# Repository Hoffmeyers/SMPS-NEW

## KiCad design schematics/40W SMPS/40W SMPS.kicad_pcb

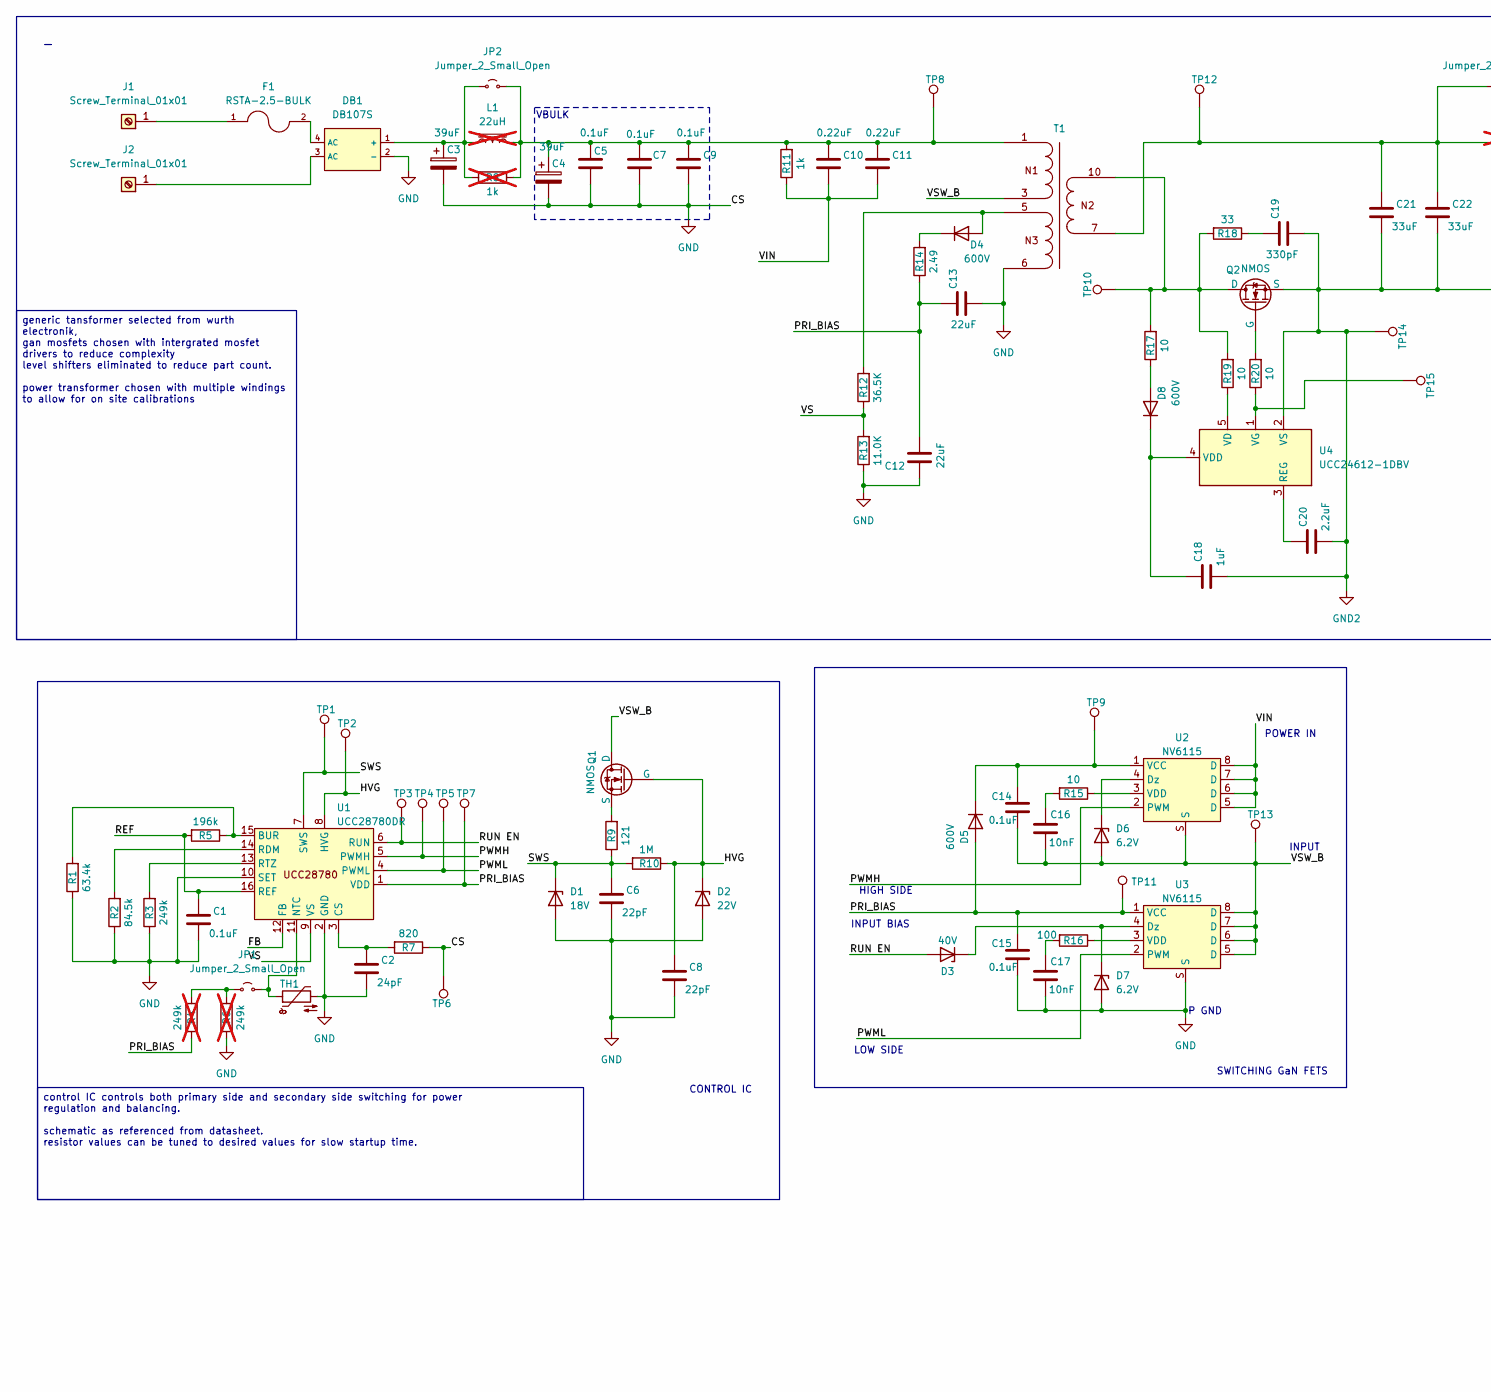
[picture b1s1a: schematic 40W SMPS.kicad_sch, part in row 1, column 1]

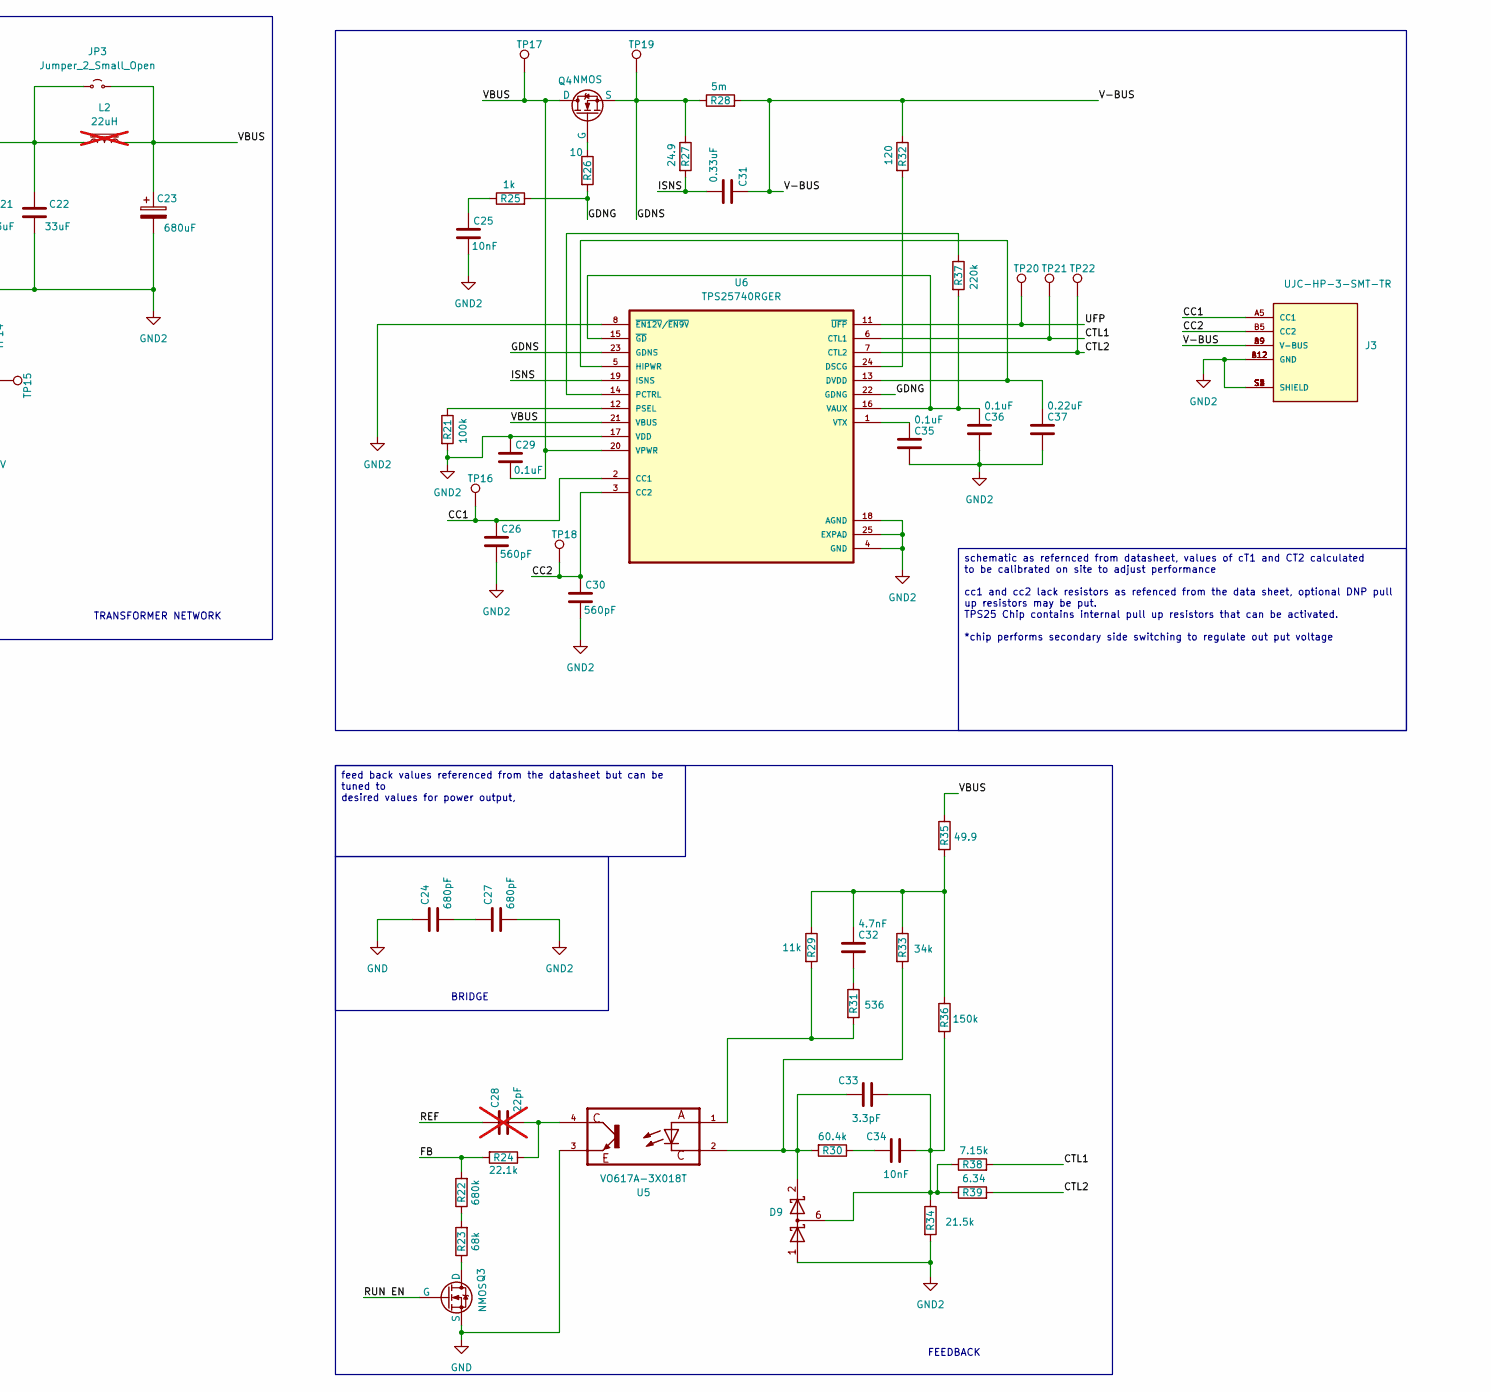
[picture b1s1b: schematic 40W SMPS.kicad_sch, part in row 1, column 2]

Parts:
C1, C5, C7, C9, C14, C15, C29, C35, C36: 0.1uF; C_0603; LCSC C14663
C2: 24pF; C_0603; LCSC C1654
C3, C4: 39uF; CP_Radial_D8.0mm_P3.80mm; LCSC C6718369
C6, C8: 22pF; C_0603; LCSC C1653
C10, C11, C37: 0.22uF; C_0603; LCSC C64705
C12, C13: 22uF; C_0603; LCSC C86295
C16, C17, C25, C34: 10nF; C_0603; LCSC C100042
C18: 1uF; C_0603; LCSC C15849
C19: 330pF; C_0603; LCSC C62784
C20: 2.2uF; C_0603; LCSC C23630
C21, C22: 33uF; C_CASE-A-3216-18(mm); LCSC C7186
C23: 680uF; CP_Radial_D8.0mm_P3.80mm; LCSC C88760
C24, C27: 680pF; C_0603; LCSC C30816
C26, C30: 560pF; C_0603; LCSC C519565
C28: 22pF; C_0603; LCSC C1653; not fitted
C31: 0.33uF; C_0603; LCSC C7419419
C32: 4.7nF; C_0603; LCSC C1621
C33: 3.3pF; C_0603; LCSC C882553
D1: 18V; SBR130S3-7; LCSC C117949
D2: 22V; SBR130S3-7; LCSC C117949
D3: 40V; DIO_MBRAD1045H; LCSC C19852660
D4, D5, D8: 600V; D_0603_1608Metric; LCSC C142698
D6, D7: 6.2V; SBR130S3-7; LCSC C117949
D9: D_Schottky_Dual_Series_CAK; SOT-363_SC-70-6; LCSC C96225
DB1: DB107S; DBS_L8.2-W6.4-P5.10-LS10.0-BL; Reverse Voltage (Vr) 1kV; Forward Voltage (Vf@If) 1.1V@1A; Part DB107S; LCSC C5377
F1: RSTA-2.5-BULK; FUSE_RST-1-BULK; PARTREV Jan2019; digikey 5923-RSTA2.5BULK-ND
J1, J2: Screw_Terminal_01x01; PinHeader_1x01_P2.54mm_Vertical
J3: UJC-HP-3-SMT-TR; CUI_UJC-HP-3-SMT-TR; PARTREV 04/30/2020; LCSC UJC-HP-3-SMT-TR:CUI_UJC-HP-3-SMT-TR
JP1, JP2, JP3: Jumper_2_Small_Open; SolderJumper-2_P1.3mm_Open_RoundedPad1.0x1.5mm
L1, L2: 22uH; PinHeader_1x02_P2.54mm_Vertical; not fitted
Q1, Q3: NMOS; SOT-23; LCSC C460213
Q2, Q4: NMOS; TRANS_CSD18543Q3A; LCSC C2876538
R1: 63.4k; R_0402_1005Metric_Pad0.72x0.64mm_HandSolder; LCSC C852877
R2: 84.5k; R_0402_1005Metric_Pad0.72x0.64mm_HandSolder; LCSC C4114738
R3: 249k; R_0402_1005Metric_Pad0.72x0.64mm_HandSolder; LCSC C2984416
R4, R6: 249k; R_0603_1608Metric; not fitted
R5: 196k; R_0402_1005Metric_Pad0.72x0.64mm_HandSolder; LCSC C852585
R7: 820; R_0402_1005Metric_Pad0.72x0.64mm_HandSolder; LCSC C137933
R8: 1k; R_0603_1608Metric; LCSC C22548; not fitted
R9: 121; R_0603_1608Metric; LCSC C3016242
R10: 1M; R_0603_1608Metric; LCSC C105578
R11, R25: 1k; R_0603_1608Metric; LCSC C22548
R12: 36.5K; R_0603_1608Metric; LCSC C861855
R13: 11.0K; R_0603_1608Metric; LCSC C2906986
R14: 2.49; R_0603_1608Metric; LCSC C2930146
R15, R17, R19, R20: 10; R_0603_1608Metric; LCSC C109318
R16: 100; R_0603_1608Metric; LCSC C105588
R18: 33; R_0603_1608Metric; LCSC C108661
R21: 100k; R_0402_1005Metric_Pad0.72x0.64mm_HandSolder; LCSC C14675
R22: 680k; R_0603_1608Metric; LCSC C25822
R23: 68k; R_0603_1608Metric; LCSC C23231
R24: 22.1k; R_0603_1608Metric; LCSC C2960862
R26: 10; R_0402_1005Metric_Pad0.72x0.64mm_HandSolder; LCSC C109318
R27: 24.9; R_0402_1005Metric_Pad0.72x0.64mm_HandSolder; LCSC C313715
R28: 5m; R_1206_3216Metric_Pad1.30x1.75mm_HandSolder; LCSC C5240695
R29: 11k; R_0603_1608Metric; LCSC C2906986
R30: 60.4k; R_0603_1608Metric; LCSC C23089
R31: 536; R_0603_1608Metric; LCSC C861466
R32: 120; R_0402_1005Metric_Pad0.72x0.64mm_HandSolder; LCSC C22787
R33: 34k; R_0603_1608Metric; LCSC C23008
R34: 21.5k; R_0603_1608Metric; LCSC C47115979
R35: 49.9; R_0603_1608Metric; LCSC C269902
R36: 150k; R_0603_1608Metric; LCSC C2906993
R37: 220k; R_0402_1005Metric_Pad0.72x0.64mm_HandSolder; LCSC C2907013
R38: 7.15k; R_0603_1608Metric; LCSC C861562
R39: 6.34; R_0603_1608Metric; LCSC C482894
T1: EFD25_750311594; T_Wurth_WE-FB-EFD25; Part Number 750311594; LCSC C48391662
TH1: Thermistor_NTC; PinHeader_1x02_P2.54mm_Vertical
TP1, TP2, TP3, TP4, TP5, TP6, TP7, TP8, TP9, TP10, TP11, TP12, TP13, TP14, TP15, TP16, TP17, TP18, TP19, TP20, TP21, TP22: TestPoint; TestPoint_Pad_D1.0mm
U1: UCC28780DR; SOIC127P600X175-16N; LCSC C2859738
U2, U3: NV6115; TRANS_IRFH9310TRPBF; LCSC C2844954
U4: UCC24612-1DBV; SOT95P280X145-5N; LCSC C2657796
U5: VO617A-3X018T; SOIC254P1210X390-4N; LCSC C17317941
U6: TPS25740RGER; QFN50P400X400X100-25N; LCSC C544310

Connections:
/CC1: C26.1, J3.A5 (CC1), TP16.1, U6.2 (CC1)
/CC2: C30.1, J3.B5 (CC2), TP18.1, U6.3 (CC2)
/CTL1: R38.2, TP21.1, U6.6 (CTL1)
/CTL2: R39.2, TP22.1, U6.7 (CTL2)
/FB: R22.2, R24.2, U1.12 (FB)
/GDNG: R25.2, R26.2, U6.22 (GDNG)
/GDNS: Q4.3 (S), R27.1, R28.1, TP19.1, U6.23 (GDNS)
/HVG: C8.1, D2.1 (K), Q1.2 (G), R10.1, TP2.1, U1.8 (HVG)
/ISNS: C31.1, R27.2, U6.19 (ISNS)
/PRI_BIAS: C12.2, C13.1, C15.1, D5.2 (A), R4.2, R14.1, TP7.1, TP11.1, U1.1 (VDD), U3.1 (VCC)
/PWMH: TP4.1, U1.5 (PWMH), U2.2 (PWM)
/PWML: TP5.1, U1.4 (PWML), U3.2 (PWM)
/REF: C1.1, C28.1, R5.2, U1.16 (REF)
/RUN EN: D3.2 (A), Q3.2 (G), TP3.1, U1.6 (RUN)
/SWS: C6.1, D1.1 (K), R9.1, R10.2, TP1.1, U1.7 (SWS)
/UFP: TP20.1, U6.11 (~UFP)
/V-BUS: C31.2, J3.A9 (V-BUS), J3.B9 (V-BUS), R28.2, R32.1
/VBUS: C23.1, C29.2, JP3.2 (B), L2.2, Q4.1 (D), R35.1, TP17.1, U6.20 (VPWR), U6.21 (VBUS)
/VIN: C10.2, C11.2, R11.1, U2.5 (D), U2.6 (D), U2.7 (D), U2.8 (D)
/VS: R12.1, R13.2, U1.9 (VS)
/VSW_B: C14.2, C16.2, D6.2 (A), Q1.1 (D), T1.3, T1.4, TP13.1, U2.S, U3.5 (D), U3.6 (D), U3.7 (D), U3.8 (D)
GND: C1.2, C2.2, C3.2, C4.2, C5.2, C6.2, C7.2, C8.2, C9.2, C12.1, C13.2, C15.2, C17.2, C24.1, D1.2 (A), D2.2 (A), D7.2 (A), DB1.2 (-), Q3.3 (S), R1.1, R2.1, R3.1, R6.1, R7.1, R13.1, T1.6, TH1.2, TP6.1, U1.2 (GND), U1.10 (SET), U3.S, U5.3
GND2: C18.2, C19.2, C20.2, C21.2, C22.2, C23.2, C25.2, C26.2, C27.2, C29.1, C30.2, C35.2, C36.2, C37.2, D9.1 (A), J3.A12 (GND), J3.B12 (GND), J3.S1 (SHIELD), J3.S2 (SHIELD), J3.S3 (SHIELD), J3.S4 (SHIELD), Q2.3 (S), R21.2, R34.2, TP14.1, U4.2 (VS), U6.4 (GND), U6.8 (~EN12V/~EN9V), U6.17 (VDD), U6.18 (AGND), U6.25 (EXPAD)
unnamed: C16.1, R15.2
unnamed: C17.1, R16.2
unnamed: C19.1, R18.1
unnamed: C24.2, C27.1
unnamed: C25.1, R25.1
unnamed: C28.2, R24.1, U5.4
unnamed: C32.1, R29.1, R33.1, R35.2, R36.1
unnamed: C32.2, R31.1
unnamed: C34.1, R30.1
unnamed: D3.1 (K), D7.1 (K), U3.4 (Dz)
unnamed: D4.2 (A), R12.2, T1.5
unnamed: D4.1 (K), R14.2
unnamed: C14.1, D5.1 (K), TP9.1, U2.1 (VCC)
unnamed: D6.1 (K), U2.4 (Dz)
unnamed: D8.2 (A), R17.1
unnamed: C18.1, D8.1 (K), U4.4 (VDD)
unnamed: C33.1, D9.2 (K), R30.2, R33.2, U5.2
unnamed: C33.2, C34.2, D9.6 (common), R34.1, R36.2, R38.1, R39.1
unnamed: C3.1, DB1.1 (+), JP2.1 (A), L1.1, R8.1
unnamed: DB1.4 (AC), F1.2
unnamed: F1.1, J1.1
unnamed: DB1.3 (AC), J2.1
unnamed: JP1.1 (A), R4.1, R6.2
unnamed: JP1.2 (B), TH1.1, U1.11 (NTC)
unnamed: C4.1, C5.1, C7.1, C9.1, C10.1, C11.1, JP2.2 (B), L1.2, R8.2, R11.2, T1.1, T1.2, TP8.1
unnamed: C21.1, C22.1, JP3.1 (A), L2.1, T1.7, T1.8, T1.9, TP12.1
unnamed: Q1.3 (S), R9.2
unnamed: Q2.1 (D), R17.2, R18.2, R19.2, T1.10, T1.11, T1.12, TP10.1
unnamed: Q2.2 (G), R20.2
unnamed: Q3.1 (D), R23.1
unnamed: Q4.2 (G), R26.1
unnamed: R22.1, R23.2
unnamed: R29.2, R31.2, U5.1
unnamed: R1.2, R5.1, U1.15 (BUR)
unnamed: C2.1, R7.2, U1.3 (CS)
unnamed: R2.2, U1.14 (RDM)
unnamed: R3.2, U1.13 (RTZ)
unnamed: R15.1, U2.3 (VDD)
unnamed: R16.1, U3.3 (VDD)
unnamed: C20.1, U4.3 (REG)
unnamed: R19.1, U4.5 (VD)
unnamed: R20.1, TP15.1, U4.1 (VG)
unnamed: R32.2, U6.24 (DSCG)
unnamed: C37.1, U6.5 (HIPWR), U6.13 (DVDD)
unnamed: R37.1, U6.14 (PCTRL)
unnamed: R21.1, U6.12 (PSEL)
unnamed: C36.1, R37.2, U6.15 (~GD), U6.16 (VAUX)
unnamed: C35.1, U6.1 (VTX)

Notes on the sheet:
TRANSFORMER NETWORK
BRIDGE
P GND
CONTROL IC
INPUT BIAS
HIGH SIDE
INPUT
FEEDBACK
POWER IN
SWITCHING GaN FETS
VBULK
LOW SIDE
control IC controls both primary side and secondary side switching for power regulation and balancing. schematic as referenced from datasheet. resistor values can be tuned to desired values for slow startup time.
schematic as refernced from datasheet, values of cT1 and CT2 calculated to be calibrated on site to adjust performance cc1 and cc2 lack resistors as refenced from the data sheet, optional DNP pull up resistors may be put. TPS25 Chip contains internal pull up resistors that can be activated. *chip p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
feed back values referenced from the datasheet but can be tuned to desired values for power output,
generic tansformer selected from wurth electronik, gan mosfets chosen with intergrated mosfet drivers to reduce complexity level shifters eliminated to reduce part count. power transformer chosen with multiple windings to allow for on site calibrations

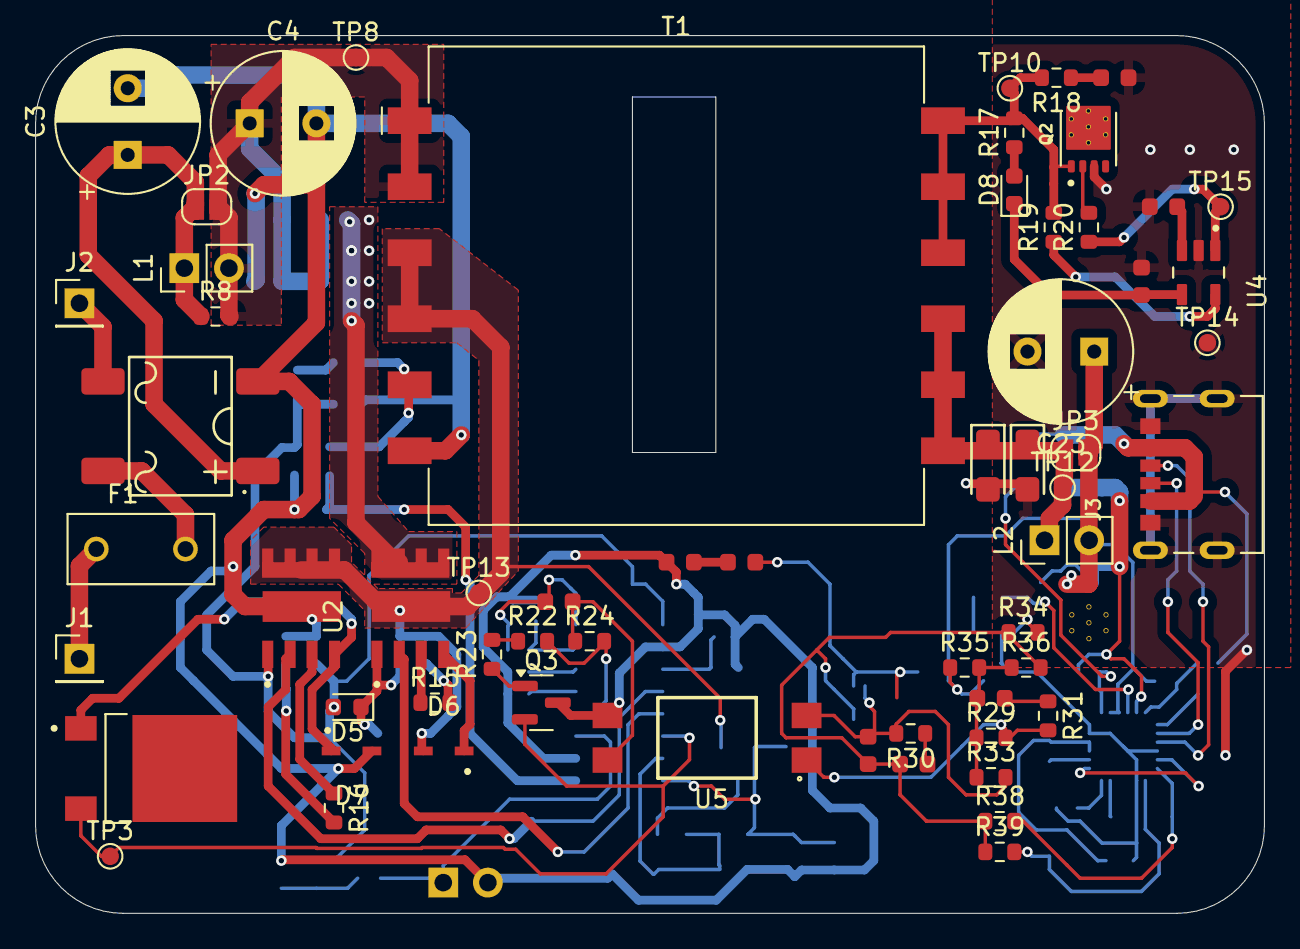
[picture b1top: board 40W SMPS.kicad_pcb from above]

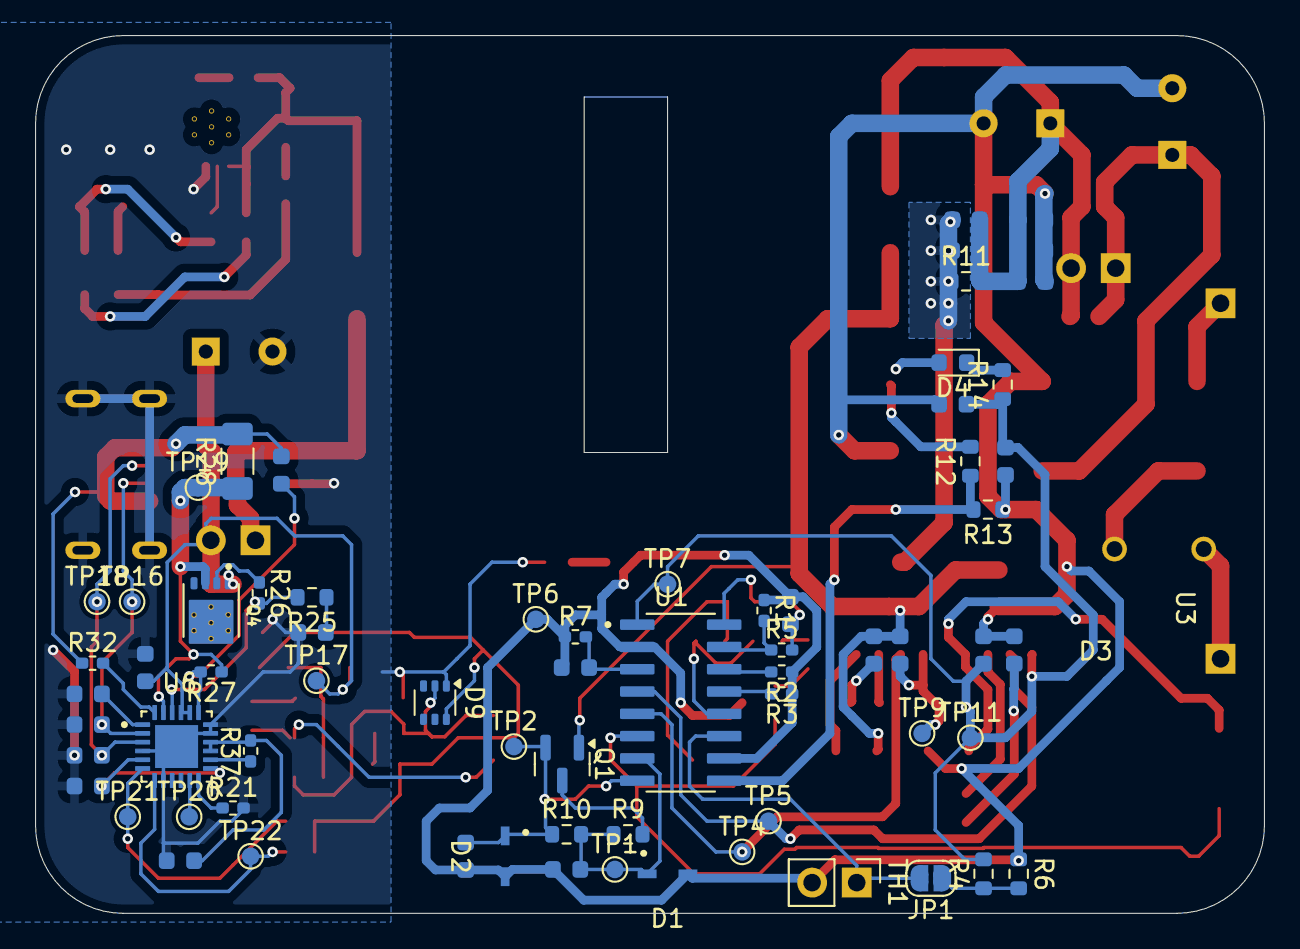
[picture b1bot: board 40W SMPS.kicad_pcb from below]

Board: 2 copper layers, 70.0 x 50.0 mm, 129 parts (68 on the bottom side), 71 nets.

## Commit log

2025-10-15 new design
2025-10-24 finalised board
